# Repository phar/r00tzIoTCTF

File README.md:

<pre>
installation on image, i expect this to be run as root
switch base:
create a switch user
git clone https://github.com/phar/r00tzIoTCTF --recursive
export switchuser=r00tzIoT
mv r00tzIoTCTF/switch /home/$switchuser/flaskapp
sed  "s/\/home\/pi/\/home\/$switchuser/g"  /home/$switchuser/flaskapp/daemon/switchDaemon.py   > /home/$switchuser/flaskapp/daemon/switchDaemon_written.py
sed  "s/\/home\/pi/\/home\/$switchuser/g"   r00tzIoTCTF/rpiconfig/uwsgi.ini.switch   >  /home/$switchuser/flaskapp/uwsgi.ini

add the following line to /etc/rc.local
/usr/bin/python3 /home/[switchuser]/flaskapp/daemon/switchDaemon_written.py& #note the amersand is new because daemon module flakes

#switch nginx:
sudo rm /etc/nginx/sites-enabled/default
sudo cp  r00tzIoTCTF/rpiconfig/flask_proxy  /etc/nginx/sites-enabled/
sudo ln -s /etc/nginx/sites-available/flaskapp_proxy /etc/nginx/sites-enabled/flaskapp_proxy
sed  "s/\/home\/pi/\/home\/$switchuser/g"  r00tzIoTCTF/rpiconfig/uwsgi.service  > /tmp/uwsgi.service
sudo cp /tmp/uwsgi.service   /etc/systemd/system/uwsgi.service

#switch finish:
sudo chown www-data.www-data /home/$switchuser/flaskapp -R
tar -cjvpf factory_reset.tbz flaskapp
rm -rf r00tzIoTCTF

#######
#cloud
#########
git clone https://github.com/phar/r00tzIoTCTF --recursive
#create a cloud user

export clouduser=r00tzIoT
export switchuser=r00tzIoT
mv r00tzIoTCTF/cloud /home/$clouduser/flaskapp
sed  "s/\/home\/pi/\/home\/$clouduser/g"  r00tzIoTCTF/rpiconfig/uwsgi.ini.cloud   >  /home/$clouduser/flaskapp/uwsgi.ini

#cloud nginx
sudo rm /etc/nginx/sites-enabled/default
sudo cp  r00tzIoTCTF/rpiconfig/flask_proxy nano /etc/nginx/sites-enabled/
sudo ln -s /etc/nginx/sites-available/flaskapp_proxy /etc/nginx/sites-enabled/flaskapp_proxy
sed  "s/\/home\/pi/\/home\/$clouduser/g"  r00tzIoTCTF/rpiconfig/uwsgi.service  > /tmp/uwsgi.service
sudo cp /tmp/uwsgi.service   /etc/systemd/system/uwsgi.service

cloud finish:
sudo chown www-data.www-data /home/$clouduser/flaskapp -R
#make firmware update package
mv r00tzIoTCTF/switch r00tzIoTCTF/flaskapp
sudo chown www-data r00tzIoTCTF/flaskapp -R
sed  "s/\/home\/pi/\/home\/$switchuser/g"   r00tzIoTCTF/rpiconfig/uwsgi.ini.switch   >  flaskapp/uwsgi.ini

sudo tar -C r00tzIoTCTF/ --exclude='flaskapp/configs' --exclude='/flaskapp/logs' -cjvpf /home/$clouduser/flaskapp/upgrade_package.tbz flaskapp 
sudo chown   www-data.www-data  /home/$clouduser/flaskapp/upgrade_package.tbz
#cleanup
rm -rf r00tzIoTCTF

#notes:
	if you want to run them locally to test them, you will need to manually run the daemon otherwise actions taken in the cloud will never update on the switch
and update checks will never happen

----------------------------------
TODO test normal workflow
TODO cloud heartbeat frequency
TODO about page on the switch should be populated with something
TODO factory restore needs testing/debugging
TODO factory reset option in gui, actually check session to prevent trivial reset

</pre>

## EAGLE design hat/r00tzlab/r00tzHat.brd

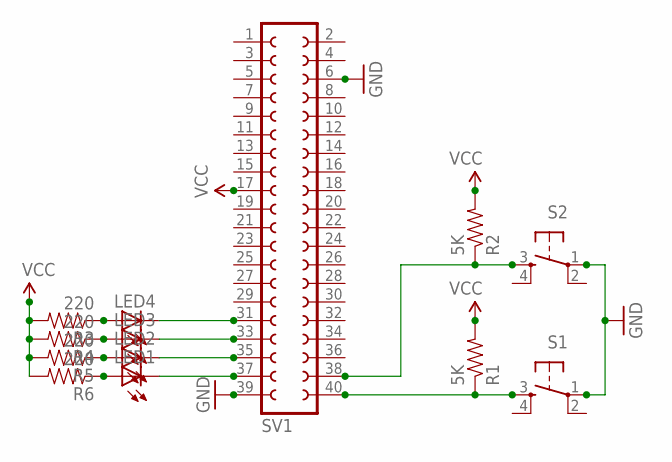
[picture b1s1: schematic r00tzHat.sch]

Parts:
LED1, LED2, LED3, LED4: LEDCHIPLED_1206; CHIPLED_1206
R1, R2: 5K; 0402-RES
R3, R4, R5, R6: 220; 0402-RES
S1, S2: TAC_SWITCHSMD; TACTILE_SWITCH_SMD
SV1: FE20-2

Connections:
GND: S1.1, S2.1, SV1.6, SV1.39
unnamed: LED1.C, SV1.37
unnamed: LED2.C, SV1.35
unnamed: LED3.C, SV1.33
unnamed: LED4.C, SV1.31
unnamed: LED4.A, R3.1
unnamed: LED3.A, R4.1
unnamed: LED2.A, R5.1
unnamed: LED1.A, R6.1
unnamed: R1.1, S1.3, SV1.40
unnamed: R2.1, S2.3, SV1.38
VCC: R1.2, R2.2, R3.2, R4.2, R5.2, R6.2, SV1.17

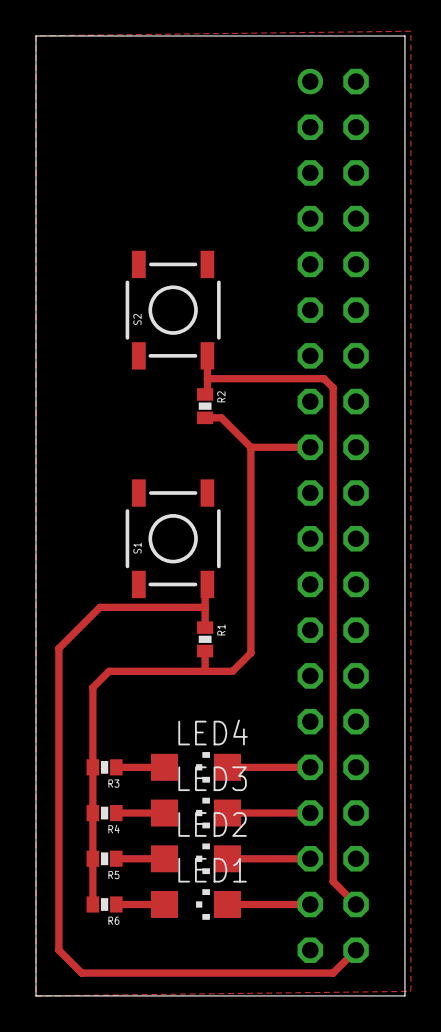
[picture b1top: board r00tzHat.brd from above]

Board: 2 copper layers, 20.5 x 53.3 mm, 13 parts (1 on the bottom side), 12 nets.

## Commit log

2020-03-29 initial checkin
2020-03-31 closer to finishing new user registration
2020-04-01 partial, broken checkin to checkpoint my status
2020-04-01 still some things broken, checking in screenshots
2020-04-01 cleanups
2020-04-03 house cleaning
2020-04-03 tweaks plus admin interface
2020-04-06 mostly working
2020-04-06 fixing bugs
2020-04-06 more stuff
2020-04-08 sync
2020-04-09 bug fixes, html changes
2020-04-10 finish config restore, minor cleanups`:
2020-04-10 more tweaks, swapped out screenshots
2020-04-11 initial hardware integration
2020-04-11 schematic checkin
2020-04-12 getting some blinkin lights
2020-04-15 implemented hat driver into code, added support for self signed TLS
2020-04-15 finished up admin log view
2020-04-20 flushing changes
2020-04-21 now supporting lights that have color.. for some reason
2020-04-23 finish supporting color in js
2020-04-23 adding file`
2020-04-24 integration fixes
2020-04-25 ugh.. painted out of corner
2020-04-27 pre-cleanup-checkin
2020-04-27 cleaning
2020-04-27 more cleaning
2020-04-27 i think stuff works well enough to share, more cleaning needed i think
2020-04-27 html tag in readme
2020-04-28 debugging and cleaning
2020-04-28 switchdaemon fixes
2020-04-28 switch daemon
2020-05-06 adjusting for prepared image
2020-05-06 more rpi image tweaks to agree with rpi build:wq
2020-05-06 disable uwsgi logging by default
2020-05-06 fixing missing admin login via get param/admin logviews
2020-05-06 i think this might be a close to a release candidate
2020-05-10 syncing cloud configs with image
2020-05-13 cloud integration and bugfixes
2020-05-13 missed the slight api change for updates
2020-05-13 removing python daemon module..
2020-05-26 fixing typos, actualy working out firmware update
2020-05-26 more upgrade fix
2020-06-10 adding dmx submodule
2020-06-16 initial dmxswitch update for debugging
2020-06-17 more minor fixes
2020-06-25 dmx color change w/o switching light off and on again
2020-06-25 factory restore path bug fix
2020-06-28 firmware update debugging
2020-06-28 fw update image prep was missing uswgi configs: # Please enter the commit message for your changes. Lines starting # with '#' will be ignored, and an empty message aborts the commit. # # Committer: p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

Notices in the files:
parts and their libraries:
SparkFun: Licensing: CC v3.0 Share-Alike You are welcome to use this library for commercial purposes.
